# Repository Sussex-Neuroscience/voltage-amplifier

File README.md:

# Arduino Due compatible voltage amplifier

Hi! This repository contains all the necessary documents to replicate an arduino Due compatible voltage amplifier.

This system was developed as part of a research project of the [Ward Lab](http://www.sussex.ac.uk/profiles/92444/research). It is to be used with a stimulus isolation adaptor from BIOPAC, more specifically one of the models that provide isolated voltage: https://www.biopac.com/product/stimulus-isolation-adapters/

The idea is simple, we use the true analog output ports from the Arduino DUE as an independent channel and amplify their signals using Operational amplifiers. In this case two [LM741](https://www.biopac.com/product/stimulus-isolation-adapters/) from Texas instruments. Using serial communication the system can be controlled in various ways, from the Arduino IDE to whatever programming languages (Python, Matlab, etc).

In [Hardware](./hardware) readers are going to find the information necessary (gerbers, bill of materials) to order components and replicate the board.

In [code](./code) readers are going to find the arduino code needed to for sending serial commands to the arduino and getting voltage signals out of the 2 different analog channels. There is also example code in Matlab to show how to control the arduino (readers should note that the Matlab Arduino libraries are not being used. Just plain serial commands).

---

## setting up system (bare minimum):

1. Install Arduino IDE and its drivers: https://www.arduino.cc/en/Main/Software
2. Install the arduino DUE support (SAM boards) using the board manager tool in the IDE (tools > boards > boards_manager)

3. Download and unzip the serial communication library (https://github.com/kroimon/Arduino-SerialCommand). Place the unzipped folder on the Arduino Libraries folder.

4. test that everything is working by opening the serial communication library example code and uploading it to the board.

  - Emit a couple of commands (eg: ON, OFF, HELLO) using the serial monitor (can be accessed via the icon on the top right corner of the Arduino IDE).

5. Upload the "SerialCommands" sketch to the arduino board and open the Serial monitor

- **channel1**  
    - DUR1 ZZZ sets the stimulus duration in milliseconds (where ZZZ should be replaced by the time desired) for channel 1.    
      - ZZZ specifies the amount of time of ON and OFF phase of the pulse (ie ZZZ=10 defines a pulse that is 10ms on and 10ms off).
    - REP1 WWW sets the number of pulses for channel 1.  
    - AMP1 YYY sets the voltage level, in between 550 and 2750 for channel 1.  
    - GO1 starts the stimulation in channel 1.  

- **channel 2**  
    - DUR2 ZZZ sets the stimulus duration in milliseconds(where ZZZ should be replaced by the time desired) for channel 2.    
      - ZZZ specifies the amount of time of ON and OFF phase of the pulse (ie ZZZ=10 defines a pulse that is 10ms on and 10ms off).    
    - REP2 WWW sets the number of pulses for channel 2.    
    - AMP2 YYY sets the voltage level, in between 550 and 2750 milliVolts for channel 2.    
    - GO2 starts the stimulation in channel 2.    

---

### Hardware considerations:

- The BIOPAC system takes voltage signals as inputs to create the electric stimulus. Here we are using an Arduino DUE as the system needs a true analog voltage and not PWM.
  - The arduno DUE has two DAC ports that output signals in between 0.55 and 2.75V with 12bit resolution (in other words, we can divide the 2.75-0.55 interval into 4096 discrete levels).
  - One limitation is that there is no true 0V for the ports, so we need to use a NPN transistor to interrupt the circuit and realy turn off the system.
  - [Here]((/hardware/transistor_switch/schematic.pdf)) is the diagram for the transistor switches

  ---

### ordering everything using [Kitspace.org](kitspace.org)

- To make it easy for readers to source all necessary components, we've uploaded this project to Kitspace, an open source project that simplifies the ordering process. Follow this link https://kitspace.org/boards/github.com/sussex-neuroscience/voltage-amplifier/ to go to the project page on Kitspace.

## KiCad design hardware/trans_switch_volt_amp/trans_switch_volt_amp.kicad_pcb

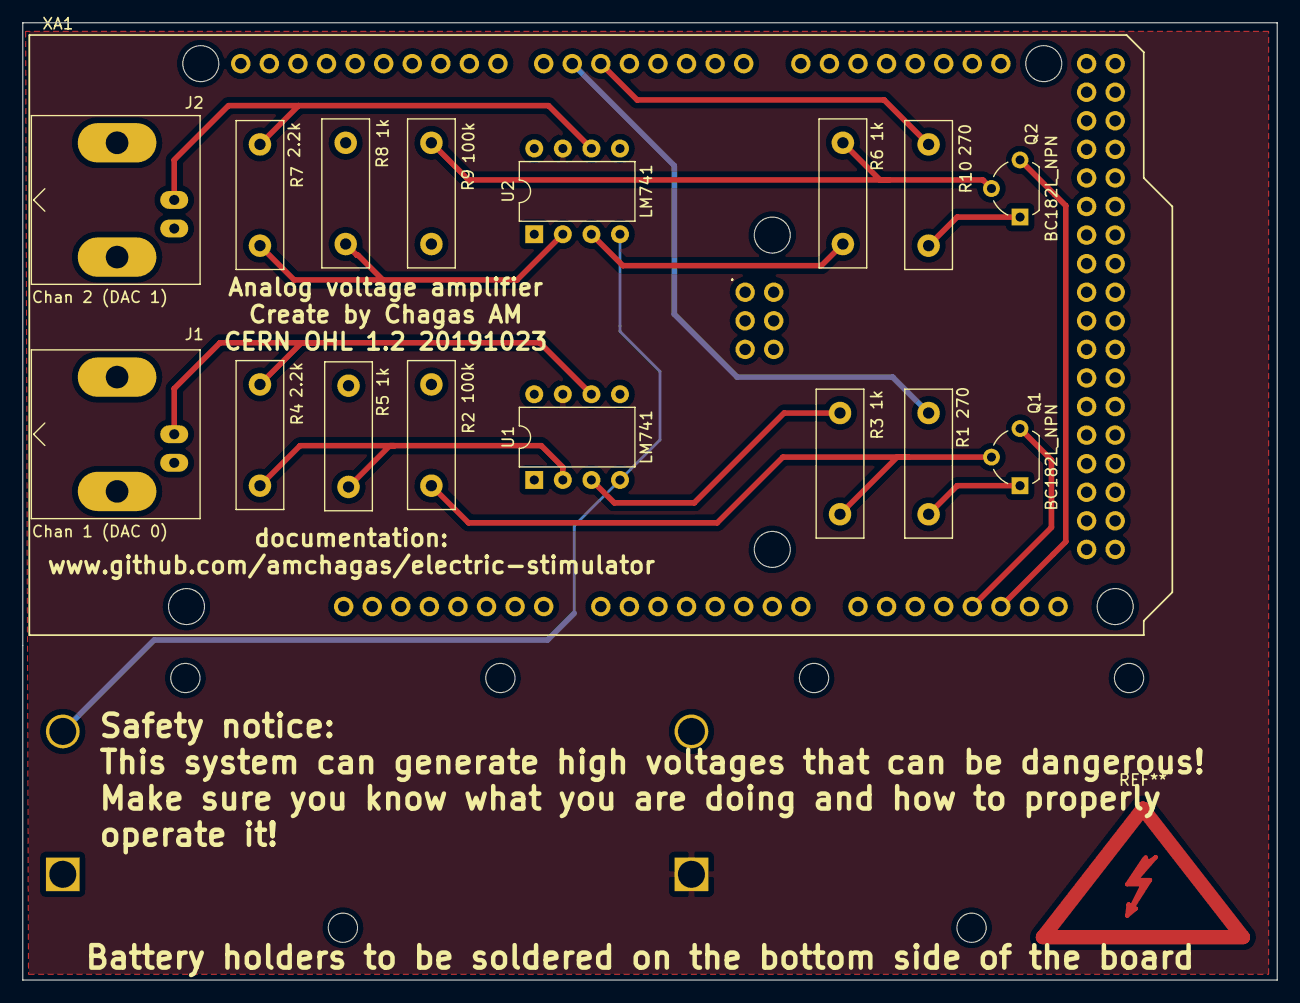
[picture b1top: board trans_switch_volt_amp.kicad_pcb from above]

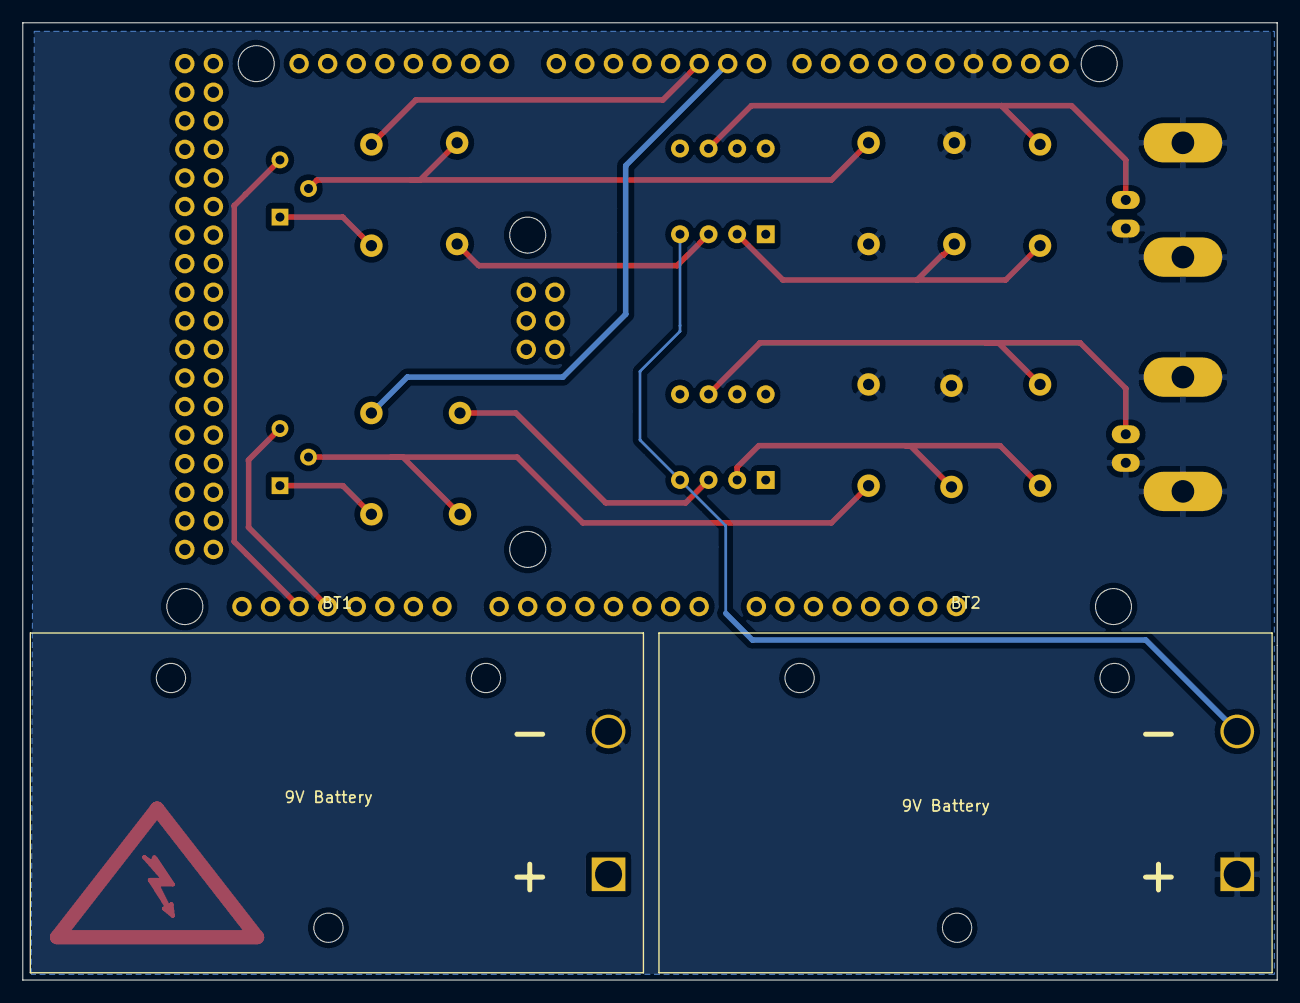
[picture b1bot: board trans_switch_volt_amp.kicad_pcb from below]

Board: 2 copper layers, 111.5 x 85.1 mm, 19 parts (2 on the bottom side), 17 nets.

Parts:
BT1, BT2: 9V Battery; BatteryHolder_Eagle_12BH611-GR
J1: Chan 1 (DAC 0); BNC_Amphenol_B6252HB-NPP3G-50_Horizontal
J2: Chan 2 (DAC 1); BNC_Amphenol_B6252HB-NPP3G-50_Horizontal
Q1, Q2: BC182L_NPN; TO-92L_Wide
R1, R10: 270; R_Box_L13.0mm_W4.0mm_P9.00mm
R2, R9: 100k; R_Box_L13.0mm_W4.0mm_P9.00mm
R3, R5, R6, R8: 1k; R_Box_L13.0mm_W4.0mm_P9.00mm
R4, R7: 2.2k; R_Box_L13.0mm_W4.0mm_P9.00mm
U1, U2: LM741; DIP-8_W7.62mm
XA1: Arduino_Due_Shield

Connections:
GND: BT1.2, BT2.1, J1.2, J2.2, R2.2, R5.1, R8.1, R9.2, XA1.GND1
unnamed: BT1.1, U1.7, U2.7
unnamed: BT2.2, U1.4, U2.4
unnamed: J1.1, R4.2, U1.6
unnamed: J2.1, R7.2, U2.6
unnamed: Q1.1, R1.1
unnamed: Q1.2, R2.1, R3.1
unnamed: Q1.3, XA1.DAC0
unnamed: Q2.1, R10.1
unnamed: Q2.2, R6.1, R9.1
unnamed: Q2.3, XA1.DAC1
unnamed: R1.2, XA1.D6
unnamed: R3.2, U1.3
unnamed: R4.1, R5.2, U1.2
unnamed: R6.2, U2.3
unnamed: R7.1, R8.2, U2.2
unnamed: R10.2, XA1.D5

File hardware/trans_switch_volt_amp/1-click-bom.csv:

References,Qty,Description,Manufacturer,MPN,Manufacturer_1,MPN_2,Manufacturer_3,MPN_4,Manufacturer_5,MPN_6,Manufacturer_7,MPN_8,Digikey,Mouser,RS,Newark,Farnell
R1;R10,2,270 ohm,RS-pro,707-7625,,,,,,,,,,,707-7625,,
R2;R9 ,2,100k ohm,TE connectivity,LR1F100k,,,,,,,,,,,125-1168,,
R3;R5;R6;R8,4,1k ohm,Vishay,MRS25000C1001FCT00,,,,,,,,,,,683-3165,,
R4;R7,2,2.2k ohm,Vishay,MRS25000C2201FCT00,,,,,,,,,,,683-3449,,
"J1,J2",2,BNC connector,Amphenol,B6252H7-NPP3G-50,,,,,,,,,,,700-9423,,
"Q1,Q2",2,BC182L NPN transistor,,,,,,,,,,,,,,,
U1;U2,2,IC socket,Assmann,A 08-LC-TT,,,,,,,,,,,674-2435,,
U1;U2,2,LM741 opamp,Texas instruments,LM741CN/NOPB,,,,,,,,,,,535-9969,,
B1;B2,2,Battery clips,Keystone,1294,,,,,,,,,,,172-5845,,

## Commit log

2019-09-22 add node_modules to gitignore and update readme
    Node_modules has many js packages that shouldn't be tracked by git
    readme was updated to let people know what is the documentation package
    used and where to actually find the documentation.
2019-09-22 to communicate with the arduino, we are using a serial library
    This library sets a token system and we implemented functions for the
    Python side of things to wait for a confirmation token.
2019-09-24 Updated documentation and electronics schematics
2019-09-25 updated arduion code so that trains of pulses are given, added the option for a second port
2019-09-25 ports can now be programatically selected
2019-10-07 updated arduino code so that it can trigger two channels
2019-10-07 add matlab code to communicate with Arduino
2019-10-07 updated electronic schematics, exported schematics pdf and made a commented photo of the protoboard
2019-10-08 update instructions on how to run the stimulation
2019-10-14 updated matlab code, got rid of serial command not running as part of a function
2019-10-16 update code on arduino and matlab due to latest testing. Small changes to serial port used
2019-10-16 schematics for 2 channel voltage amplifier
2019-10-16 start on implementing an arduino shield for the stimulator
2019-10-21 created shield for the amplifier system
2019-10-23 finish writing warnings and lincenses on the board
2019-11-07 start BOM
2019-11-25 start writing down the BOM for the electric stimulator
2019-11-27 clean up repository and add 1-click-bom.csv
2019-12-06 update board and fixed transistor bug
2020-01-10 remove old version of board
2020-01-10 update bom
2020-01-10 add kitspace.yaml
2020-01-10 clean up readme
2020-01-10 validated version of yaml
2020-01-10 update arduino code so that input in in mV.
2020-01-10 update arduino code so that input in is mV. and update matlab code
2020-01-10 update readme with information that voltage should be given in millivolts
2020-01-10 You accidentally an s
2020-01-10 organize location of resistor indicators
2020-01-10 update backup
2020-01-10 update readme with link to kitspace
2020-02-29 add first version of manifest and featured image
2020-02-29 more changes
2020-02-29 update manifest yml
2021-04-14 a bit of housekeeping, changing durations to microsseconds and voltages to millivolts. Correcting map function

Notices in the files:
hardware/trans_switch_volt_amp/trans_switch_volt_amp.kicad_pcb:
CERN OHL 1.2 20191023
